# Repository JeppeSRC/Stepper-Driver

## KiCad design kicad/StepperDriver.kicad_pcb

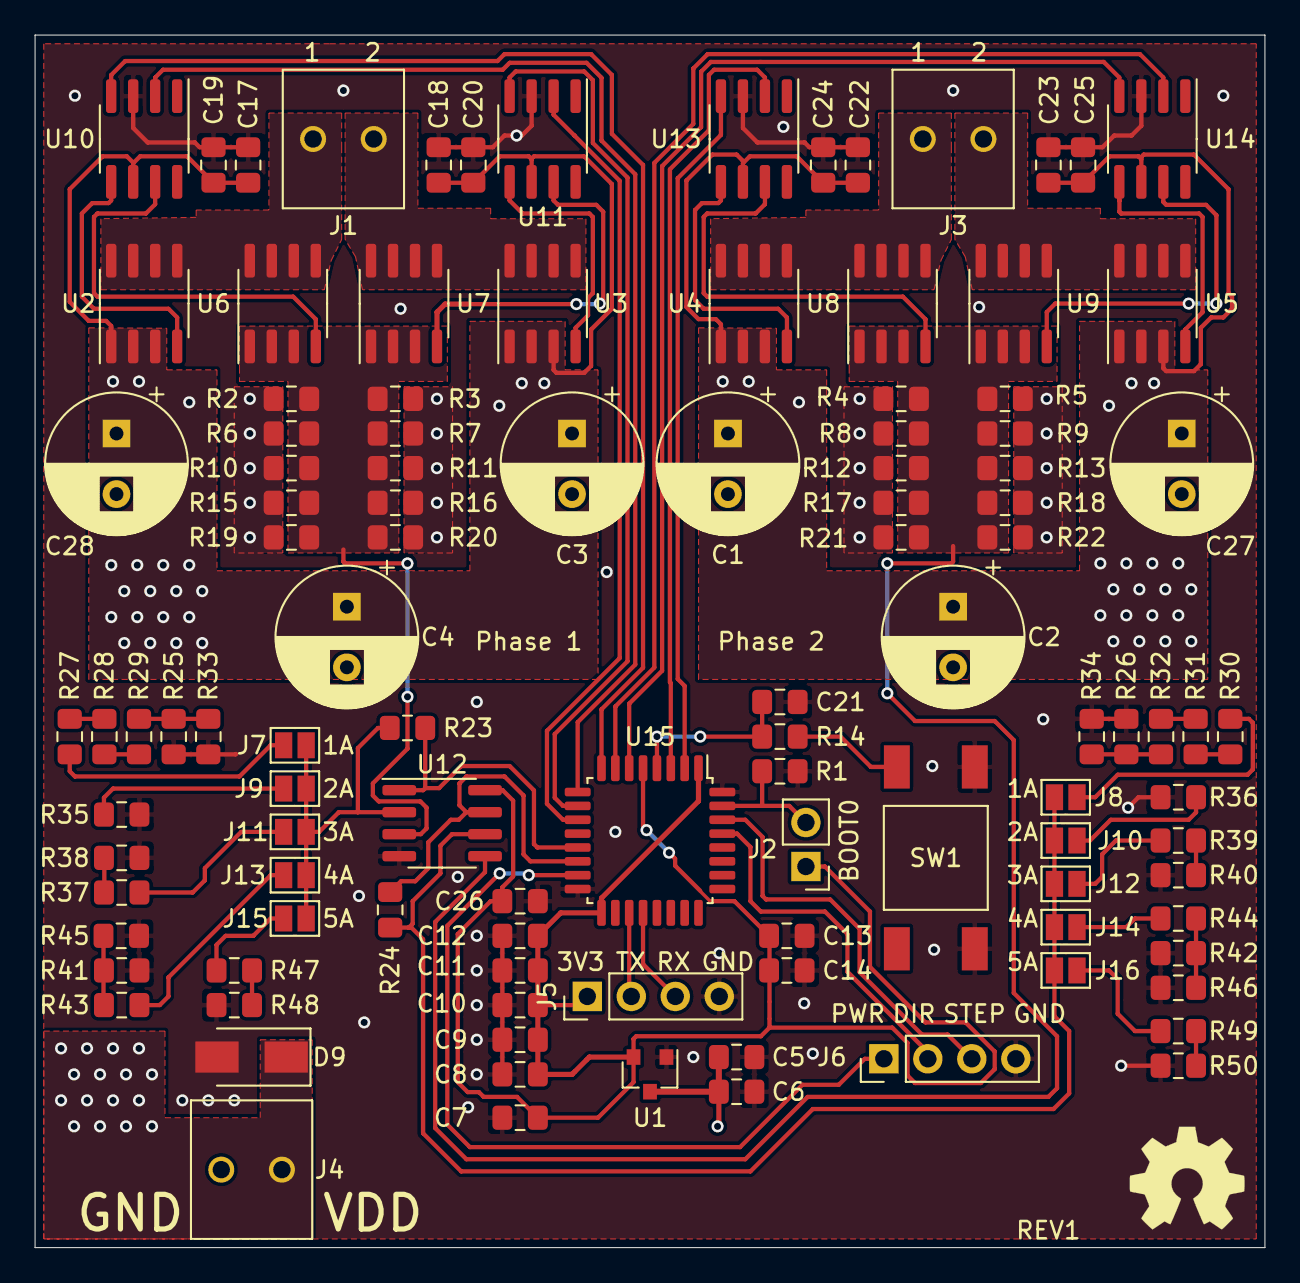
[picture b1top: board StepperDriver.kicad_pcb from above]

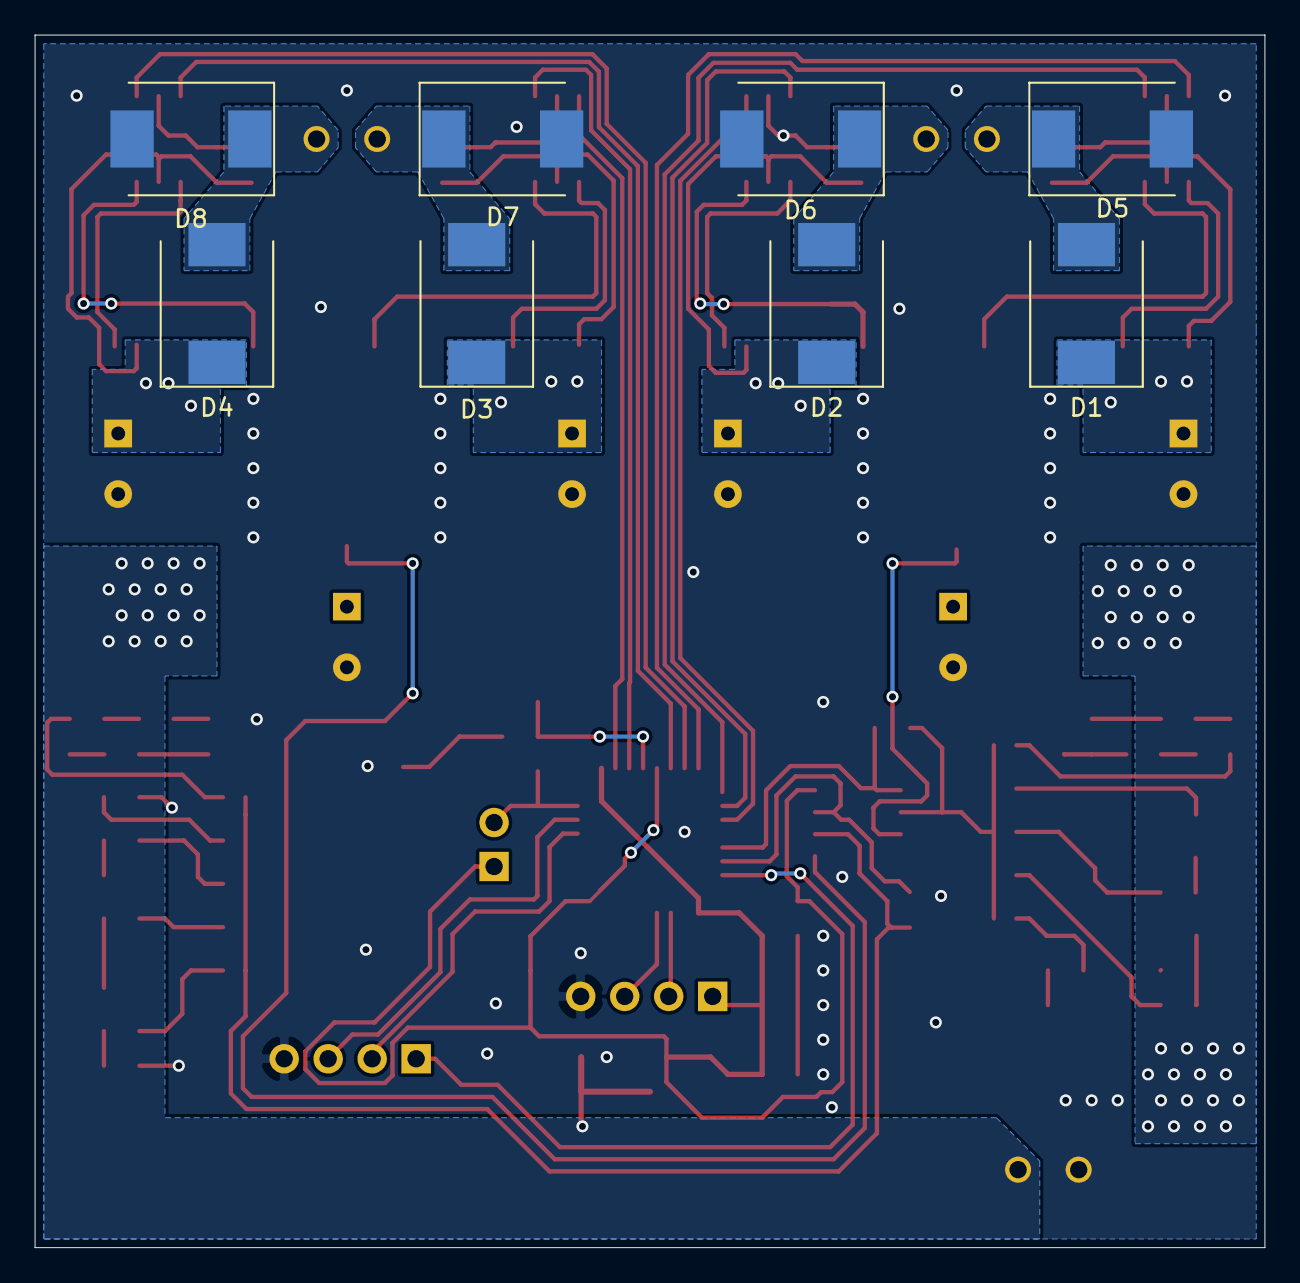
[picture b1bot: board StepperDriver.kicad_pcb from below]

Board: 2 copper layers, 71.0 x 70.0 mm, 119 parts (8 on the bottom side), 61 nets.

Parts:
C1, C3, C27, C28: 100µF; CP_Radial_D8.0mm_P3.50mm
C2, C4: 330µF; CP_Radial_D8.0mm_P3.50mm
C5, C17, C18, C22, C23: 10µF; C_0805_2012Metric_Pad1.15x1.40mm_HandSolder
C6, C7, C13, C19, C20, C24, C25: 1µF; C_0805_2012Metric_Pad1.15x1.40mm_HandSolder
C8: 4.7µF; C_0805_2012Metric_Pad1.15x1.40mm_HandSolder
C9, C10, C11, C12, C26: 100nF; C_0805_2012Metric_Pad1.15x1.40mm_HandSolder
C14, C21: 10nF; C_0805_2012Metric_Pad1.15x1.40mm_HandSolder
D1, D2, D3, D4, D5, D6, D7, D8: B540C; D_SMC
D9: SMAJ16A; D_SMA
J1: Phase 1; 20020327-C02xB0xLF
J2: BOOT0; PinHeader_1x02_P2.54mm_Vertical
J3: Phase 2; 20020327-C02xB0xLF
J4: Power In; 20020327-C02xB0xLF
J5: USART; PinHeader_1x04_P2.54mm_Vertical
J6: Control IO; PinHeader_1x04_P2.54mm_Vertical
J7, J8: 1A; SolderJumper-2_P1.3mm_Open_Pad1.0x1.5mm
J9, J10: 2A; SolderJumper-2_P1.3mm_Open_Pad1.0x1.5mm
J11, J12: 3A; SolderJumper-2_P1.3mm_Open_Pad1.0x1.5mm
J13, J14: 4A; SolderJumper-2_P1.3mm_Open_Pad1.0x1.5mm
J15, J16: 5A; SolderJumper-2_P1.3mm_Open_Pad1.0x1.5mm
NT1, NT2: NT; NetTie-2_SMD_Pad0.5mm
R1, R37, R39, R41, R42, R43, R44, R45, R46, R47, R48, R49, R50: 10k; R_0805_2012Metric_Pad1.15x1.40mm_HandSolder
R2, R3, R4, R5, R6, R7, R8, R9, R10, R11, R12, R13, R15, R16, R17, R18, R19, R20, R21, R22: 1R; R_0805_2012Metric_Pad1.15x1.40mm_HandSolder
R14, R25, R26, R27, R28, R29, R30, R31, R32, R33, R34, R38, R40: 1k; R_0805_2012Metric_Pad1.15x1.40mm_HandSolder
R23, R24: 100k; R_0805_2012Metric_Pad1.15x1.40mm_HandSolder
R35, R36: 7k15; R_0805_2012Metric_Pad1.15x1.40mm_HandSolder
SW1: Reset; LL3301NF065QG
U1: AP7370; SOT-23
U2, U3, U4, U5: FDS4435BZ; SOIC-8_3.9x4.9mm_P1.27mm
U6, U7, U8, U9: DMG4496SSS; SOIC-8_3.9x4.9mm_P1.27mm
U10, U11, U13, U14: FAN3278; SOIC-8_3.9x4.9mm_P1.27mm
U12: MCP6L02; SOIC-8_3.9x4.9mm_P1.27mm
U15: STM32F303K6Tx; LQFP-32_7x7mm_P0.8mm

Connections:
+3V3: C7.1, C26.2, J2.1, NT1.1, NT2.1, U1.2, U12.8
/BOOT0: J2.2, R1.1, U15.31
/CurrentSelection/P1_GAIN: J7.1, J9.1, J11.1, J13.1, J15.1, R23.2, U12.2
/CurrentSelection/P2_GAIN: J8.1, J10.1, J12.1, J14.1, J16.1, R24.1, U12.6
/IN_DIR: J6.2, U15.29
/IN_PWR: J6.1, U15.15
/IN_STEP: J6.3, U15.30
/IP1: R23.1, U12.1, U15.13
/IP2: R24.2, U12.7, U15.14
/P1.1: D1.2, D5.1, J1.2, U2.5, U2.6, U2.7, U2.8, U6.5, U6.6, U6.7, U6.8
/P1.2: D2.2, D6.1, J1.1, U3.5, U3.6, U3.7, U3.8, U7.5, U7.6, U7.7, U7.8
/P1_1: U10.4, U15.8
/P1_2: U10.2, U15.9
/P1_3: U11.4, U15.10
/P1_4: U11.2, U15.11
/P1_FET1: U2.4, U10.5
/P1_FET2: U6.4, U10.7
/P1_FET3: U3.4, U11.5
/P1_FET4: U7.4, U11.7
/P1_SENSE: R2.2, R3.1, R6.2, R7.1, R10.2, R11.1, R15.2, R16.1, R19.2, R20.1, U6.1, U6.2, U6.3, U7.1, U7.2, U7.3, U12.3
/P2.1: D3.2, D7.1, J3.2, U4.5, U4.6, U4.7, U4.8, U8.5, U8.6, U8.7, U8.8
/P2.2: D4.2, D8.1, J3.1, U5.5, U5.6, U5.7, U5.8, U9.5, U9.6, U9.7, U9.8
/P2_1: U13.4, U15.2
/P2_2: U13.2, U15.3
/P2_3: U14.4, U15.6
/P2_4: U14.2, U15.7
/P2_FET1: U4.4, U13.5
/P2_FET2: U8.4, U13.7
/P2_FET3: U5.4, U14.5
/P2_FET4: U9.4, U14.7
/P2_SENSE: R4.2, R5.1, R8.2, R9.1, R12.2, R13.1, R17.2, R18.1, R21.2, R22.1, U8.1, U8.2, U8.3, U9.1, U9.2, U9.3, U12.5
/RST: C21.2, R14.1, U15.4
/USART_RX: J5.3, U15.20
/USART_TX: J5.2, U15.19
/VDD1: C8.1, C9.1, C10.1, C11.1, C12.1, J5.1, NT1.2, U15.1, U15.17
/VDDA: C13.1, C14.1, NT2.2, U15.5
GND: C1.2, C2.2, C3.2, C4.2, C5.2, C6.1, C7.2, C8.2, C9.2, C10.2, C11.2, C12.2, C13.2, C14.2, C17.2, C18.2, C19.2, C20.2, C21.1, C22.2, C23.2, C24.2, C25.2, C26.1, C27.2, C28.2, D5.2, D6.2, D7.2, D8.2, D9.2, J4.1, J5.4, J6.4, R1.2, R2.1, R3.2, R4.1, R5.2, R6.1, R7.2, R8.1, R9.2, R10.1, R11.2, R12.1, R13.2, R15.1, R16.2, R17.1, R18.2, R19.1, R20.2, R21.1, R22.2, R25.1, R26.1, R33.1, R34.1, R35.1, R36.1, R38.1, R40.1, R41.1, R42.1, R45.1, R46.1, R48.1, R50.1, SW1.1, U1.1, U10.3, U11.3, U12.4, U13.3, U14.3, U15.16, U15.32
unnamed: J7.2, R27.2
unnamed: J8.2, R30.2
unnamed: J9.2, R35.2
unnamed: J10.2, R36.2
unnamed: J11.2, R37.2
unnamed: J12.2, R39.2
unnamed: J13.2, R43.2
unnamed: J14.2, R44.2
unnamed: J15.2, R47.2
unnamed: J16.2, R49.2
unnamed: R14.2, SW1.2
unnamed: R25.2, R29.1, R33.2
unnamed: R26.2, R32.1, R34.2
unnamed: R27.1, R28.2
unnamed: R28.1, R29.2
unnamed: R30.1, R31.2
unnamed: R31.1, R32.2
unnamed: R37.1, R38.2
unnamed: R39.1, R40.2
unnamed: R41.2, R43.1, R45.2
unnamed: R42.2, R44.1, R46.2
unnamed: R47.1, R48.2
unnamed: R49.1, R50.2
VDD: C1.1, C2.1, C3.1, C4.1, C5.1, C6.2, C17.1, C18.1, C19.1, C20.1, C22.1, C23.1, C24.1, C25.1, C27.1, C28.1, D1.1, D2.1, D3.1, D4.1, D9.1, J4.2, U1.3, U2.1, U2.2, U2.3, U3.1, U3.2, U3.3, U4.1, U4.2, U4.3, U5.1, U5.2, U5.3, U10.6, U11.6, U13.6, U14.6

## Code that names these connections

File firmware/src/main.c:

/*
Pinout:
	P1_1: PA2 Output
	P1_2: PA3 Output
	P1_3: PA4 Output
	P1_4: PA5 Output

	P2_1: PF0 Output
	P2_2: PF1 Output
	P2_3: PA0 Output
	P2_4: PA1 Output

	USART_TX: PA9 Alternate or output for debugging
	USART_RX: PA10 Alternate or output for debugging

	IP1: PA7 Analog
	IP2: PB0 Analog

	IN_STEP: PB7 Input
	IN_DIR: PB6 Input
	IN_PWR: PB1 Analog
*/

#include <peripherals/gpio.h>
#include <peripherals/rcc.h>
#include <peripherals/timer.h>
#include <peripherals/cortex.h>
#include <peripherals/exti.h>

extern unsigned int CCM_START;
extern unsigned int CCM_END;
extern unsigned int LMA_CCM_START;

void move_isr_vector() {
	volatile unsigned int* start = (volatile unsigned int*)CCM_START;
	volatile unsigned int* lma = (volatile unsigned int*)LMA_CCM_START;

	unsigned int size = CCM_END - CCM_START;

	for (unsigned int i = 0; i < size; i++) {
		start[i] = lma[i];
	}

	scb_vtor(CCM_START, 1);
}

int main() {
	move_isr_vector();

	rcc_cr_pllon(0);

	while (rcc_cr_pllrdy());

	rcc_cfgr_pllmul(15);
	rcc_cfgr_pllsrc(0);
	rcc_cfgr_ppre2(0);
	rcc_cfgr_ppre1(4);
	rcc_cr_pllon(1);

	while (!rcc_cr_pllrdy());

	rcc_cfgr_sw(2);

	rcc_ahbenr();
	rcc_apb2enr();
	rcc_apb1enr();

	gpioa_mode(0, OUTPUT);
	gpioa_mode(1, OUTPUT);
	gpioa_mode(2, OUTPUT);
	gpioa_mode(3, OUTPUT);
	gpioa_mode(4, OUTPUT);
	gpioa_mode(5, OUTPUT);
	gpioa_mode(9, OUTPUT);
	gpioa_mode(10, OUTPUT);

	gpiof_mode(0, OUTPUT);
	gpiof_mode(1, OUTPUT);

	gpiob_mode(0, ANALOG);
	gpiob_mode(1, ANALOG);
	gpiob_mode(5, INPUT);
	gpiob_mode(7, INPUT);

	gpioa_output_speed(0, HIGHSPEED);
	gpioa_output_speed(1, HIGHSPEED);
	gpioa_output_speed(2, HIGHSPEED);
	gpioa_output_speed(3, HIGHSPEED);
	gpioa_output_speed(4, HIGHSPEED);
	gpioa_output_speed(5, HIGHSPEED);
	gpioa_output_speed(9, HIGHSPEED);
	gpioa_output_speed(10, HIGHSPEED);

	gpiof_output_speed(0, HIGHSPEED);
	gpiof_output_speed(1, HIGHSPEED);

	gpioa_pull_updown(0, NONE);
	gpioa_pull_updown(1, NONE);
	gpioa_pull_updown(2, NONE);
	gpioa_pull_updown(3, NONE);
	gpioa_pull_updown(4, NONE);
	gpioa_pull_updown(5, NONE);
	gpioa_pull_updown(9, NONE);
	gpioa_pull_updown(10, NONE);

	gpiob_pull_updown(6, PULLDOWN);
	gpiob_pull_updown(7, PULLDOWN);

	gpiof_pull_updown(0, NONE);
	gpiof_pull_updown(1, NONE);

	exti_interrupt_enable(7);
	exti_interrupt_enable(22);
	exti_interrupt_enable(30);

	exti_trigger_rising_enable(7);
	exti_trigger_rising_enable(22);
	exti_trigger_rising_enable(30);

	nvic_interrupt_enable(23); // EXTI9_5
	nvic_interrupt_enable(54); // TIM6
	nvic_interrupt_enable(64); // COMP2
	nvic_interrupt_enable(65); // COMP4

	tim6_init();
	tim6_psc(31);
	tim6_arr(10000);
	tim6_start();
	
	//test

	unsigned int tmp = 0;

	while (1) {
		tmp = ~tmp;
		gpioa_bsrr_port(0, tmp);
	}
	
	return 0;
}

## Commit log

2018-07-11 Updated gitignore
2018-07-11 Created Visual Micro project
2018-09-08 Show all files
2018-09-08 Changed target to ATTINY84
2018-09-08 Pin setup
2018-09-30 PCB Gerber files
2018-09-30 Moved folder
2019-09-14 Deleted everything
2019-09-14 Updated .gitignore
2019-09-14 Added kicad projecty
2019-09-14 Early specs
2019-09-14 Updated spec
2019-09-14 Added symbols
2019-09-14 Updated symbols
2019-09-15 Fixed symbol
2019-09-15 Changed specs
2019-09-15 Changed symbols to the new parts and added matching footprint
2019-09-15 Added Sens amp and pot to spec
2019-09-15 Added MCP6L02 symbol
2019-09-15 Added MCP4251 Symbol
2019-09-15 Changed order of pot inputs
2019-09-15 Added signal amp to spec
2019-09-15 Added NCS70074 symbol
2019-09-15 H Bridge
2019-09-16 Chagned MCU to STM32F303K
2019-09-16 Some mcu connections
2019-09-16 Fixed serious flaw
2019-09-16 Flipped p channel driver amps to make a positive input turn on the fet
2019-09-17 Added 3v3 ldo to spec.txt
2019-09-17 Added sqaure thing around each H bridge
2019-09-18 Added LD1086 symbol
2019-09-18 Added 3V3 regulator
2019-09-20 Changed spec
2019-09-20 Fixed incorrect symbol
2019-09-20 Back down voltage spec
2019-09-20 Replaced OpAmp with descrete MOSFET and pullups
2019-09-20 Added 10 resistors in paralell for the current shunt
2019-09-20 increased one cap to 1mF
2019-09-20 Things
2019-09-20 Aded STM32F303 datasheets
2019-09-20 Added MCU decoupeling caps
2019-09-20 Forgot one ground symbol lol
2019-09-21 Added some connectors
2019-09-22 Updated fet driver to gate driver IC
2019-09-22 Removed Vin on sheet and moved pins so I could make the hierarchical sheet smaller
2019-09-22 Redesigned H bridge to use FAN3278
2019-09-23 Removed annotation
2019-09-23 Added caps to 3v3 regulator
2019-09-23 Restruvture
2019-09-23 Re org
2019-09-23 Added page info
2019-09-23 Moved shit to make it look more symetrical
2019-09-23 Added no connects to unused MCU pins
2019-09-23 Annotated
2019-09-23 Changed H bridge block description
2019-09-23 Minor change
2019-09-23 Assigned footprint to all MLCC caps
2019-09-23 Corrected some 100µF caps that were unpolarized and change them to be polarized
2019-09-23 JK forgot some MLCC caps
2019-09-23 Footprints for 100µF caps
2019-09-23 1000µF cap footprints
2019-09-23 Swicth footprint
2019-09-26 Transient snubber
2019-09-26 Changed values of shunt resistors to 2R instead of 0R2
2019-09-26 Rewired digi pot to not make values inverted
2019-09-27 Added mpn to Ux symbols
2019-09-27 Added 1000µF MPN
2019-09-27 Added 100µF MPN
2019-09-27 Added 10µF MPN
2019-09-27 Added 4.7µF MPN
2019-09-27 Added 1µF MPN
2019-09-27 Added 100nF MPN
2019-09-27 Added 10nF MPN
2019-09-28 Flyback diodes MPN and footprint
2019-09-28 Bunch of datasheets and shit
2019-09-28 Power in connector footprint and MPN
2019-09-28 Split motor connector to one connector per phase
2019-09-28 Changed Power in symbol to scren terminal
2019-09-28 Screw terminal footprint, datasheet and mpn
2019-09-28 More mpn stuff
2019-09-29 Fixed unreadable stuff
2019-09-29 Fixed unreadable stuff 2
2019-09-29 Removed weird wire
2019-09-29 Control IO and fixed some ERC errors
2019-09-29 Removed MCP4251 and added jumpers for current selection
2019-10-01 Changed current shunt to 0.1Ohm
2019-10-01 Current selection through solder bridges
2019-10-01 Changed LD1086 to AP7370
2019-10-01 Minimum requirements
2019-10-01 Removed Resistor in series with TVS diode
2019-10-01 Changed diode footprints
2019-10-01 Fixed DMG4496SSS
2019-10-01 Fixed FDS4435BZ
2019-10-02 Swapped some pins on FET drivers
2019-10-02 Some kind of beginning of layout
2019-10-03 Digital ground for micro
2019-10-03 Changed bypassing on gate drivers
2019-10-03 Some other form of layout
2019-10-03 Fixed zone net
2019-10-03 Grid settings
2019-10-03 Changed min via size stuff
2019-10-05 Sense resistors tied to ground
2019-10-08 Changed 100µF caps to ones with higher ripple current
2019-10-08 Changed 1000µF caps to 330µF caps with higher ripple current
2019-10-08 Layout stuff
2019-10-08 Some power planes
2019-10-09 Removed 10µF caps on h bridge
2019-10-10 Fixed failöed wiring
2019-10-10 Routed Gate driver signals
2019-10-11 Fixed schematic error
2019-10-11 Removed digital ground
2019-10-11 Changed input pinout
2019-10-11 Layout pretty much done
2019-10-11 Removed thing
2019-10-12 Minor changes
2019-10-12 Added Dwgs.User layer
2019-10-12 Added layer outline to Dwgs.User layer for easier panelization
2019-10-12 Added silkscreen stuff
2019-10-12 Fixed FAN3278 datasheet
2019-10-12 Moved some traces
2019-10-12 Added thermal relief to low power pins
2019-10-19 Exported BOM
2019-10-19 Something
2019-10-19 Changed cap
2020-02-14 Moved spec.txt to documentation and downloaded all relevant datasheets
2020-02-14 Stuff
2020-02-14 Added firmware project files and startup code
2020-02-14 added aaddresses and files
2020-02-14 Added linktime optimization
2020-02-14 Idkl
2020-02-14 Implemented gpio stuff
2020-02-14 Initial comparator implementation
2020-02-15 Changed dac for comp4
2020-02-15 Renamed InitializeComparators to initialize_comparators
2020-02-15 Added newline
2020-02-15 Implemented dac1
2020-02-15 Implemented some RCC stuff
2020-02-15 Minor fixes
2020-02-15 Clock initialization
2020-02-15 Fixed bug
2020-02-15 initialized io
2020-02-16 EXTI implementation
2020-02-16 NVIC implementation
2020-02-16 Fixes
2020-02-16 TIM6 and TIM7 implementation
2020-02-16 Workaround to prevent lto from removing interrupt handlers. GCC is a peice of shit
2020-02-16 Fixed typos
2020-02-17 Renamed nvic.h/nvic.c to cortex and added scb_vtor
2020-02-17 Moved isr_vector to CCM
2020-02-17 Fixed vector table
2020-02-20 Space
2020-02-20 This might make the motor spin
2020-02-20 Removed shit and updated comment
2020-02-21 Added 512 byte alignment for ccm isr_vector in linker script
2020-02-26 Added comp_output function that reads the status of the comparator
2020-02-27 Changed what happens when current limit is reached
2020-02-27 Added some comments
2020-02-27 Changed chopper frequency to 10KHz
2020-02-27 step should change state right away
